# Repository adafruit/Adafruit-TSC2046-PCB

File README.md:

## Adafruit TSC2046 SPI Resistive Touch Screen Controller PCB

<a href="http://www.adafruit.com/products/5767"><br/>
Click here to purchase one from the Adafruit shop</a>

PCB files for the Adafruit TSC2046 SPI Resistive Touch Screen Controller. 

Format is EagleCAD schematic and board layout
* https://www.adafruit.com/product/5767

### Description

Getting touchy performance with your screen's touch screen? Resistive touch screens are incredibly popular as overlays to TFT and LCD displays. Only problem is they require a bunch of analog pins and you have to keep polling them since the overlays themselves are basically just big potentiometers. If your microcontroller doesn't have analog inputs, or maybe you want just a way more elegant controller, the TSC2046 is a nice way to solve that problem.

This breakout board features the TSC2046, which has an easy-to-use SPI interface available. There is also an interrupt pin that you can use to indicate when a touch has been detected to your microcontroller or microcomputer. It can be powered from 3-5V, so it's safe to use with 3V or 5V logic. It's a nicely designed chip and has very stable precise readings. We found it's also a lot faster than trying to do all the readings on an Arduino.

For the screens that have 1mm pitch FPC cables, you can plug the cable right into the connector. The majority of medium/large touchscreens have that kind of connector. If you have another kind of touch screen, the four X/Y contacts are available on 0.1" pitch breakouts so you can hand-solder or wire them.

Getting started is super easy with our simple TSC2046 Arduino library. Plug any 1mm-pitch 4-wire resistive touchscreen to the on-board FPC connector, then use the library example to read touch points with X, Y and Z (pressure) results returned instantaneously. There's an IRQ pin that will drop low when a touch is detected, you can use that to reduce the SPI polling.

We also break out the Busy pin, that lets you know when the chip is still reading, and the Vref pin if you want to read or change the default 2.5V reference voltage. There's also two extra ADC pins you can read, Aux (0V - VRef) and VBat (0V - 2*VRef).

### License

Adafruit invests time and resources providing this open source design, please support Adafruit and open-source hardware by purchasing products from [Adafruit](https://www.adafruit.com)!

Designed by Limor Fried/Ladyada for Adafruit Industries.

Creative Commons Attribution/Share-Alike, all text above must be included in any redistribution. 
See license.txt for additional details.

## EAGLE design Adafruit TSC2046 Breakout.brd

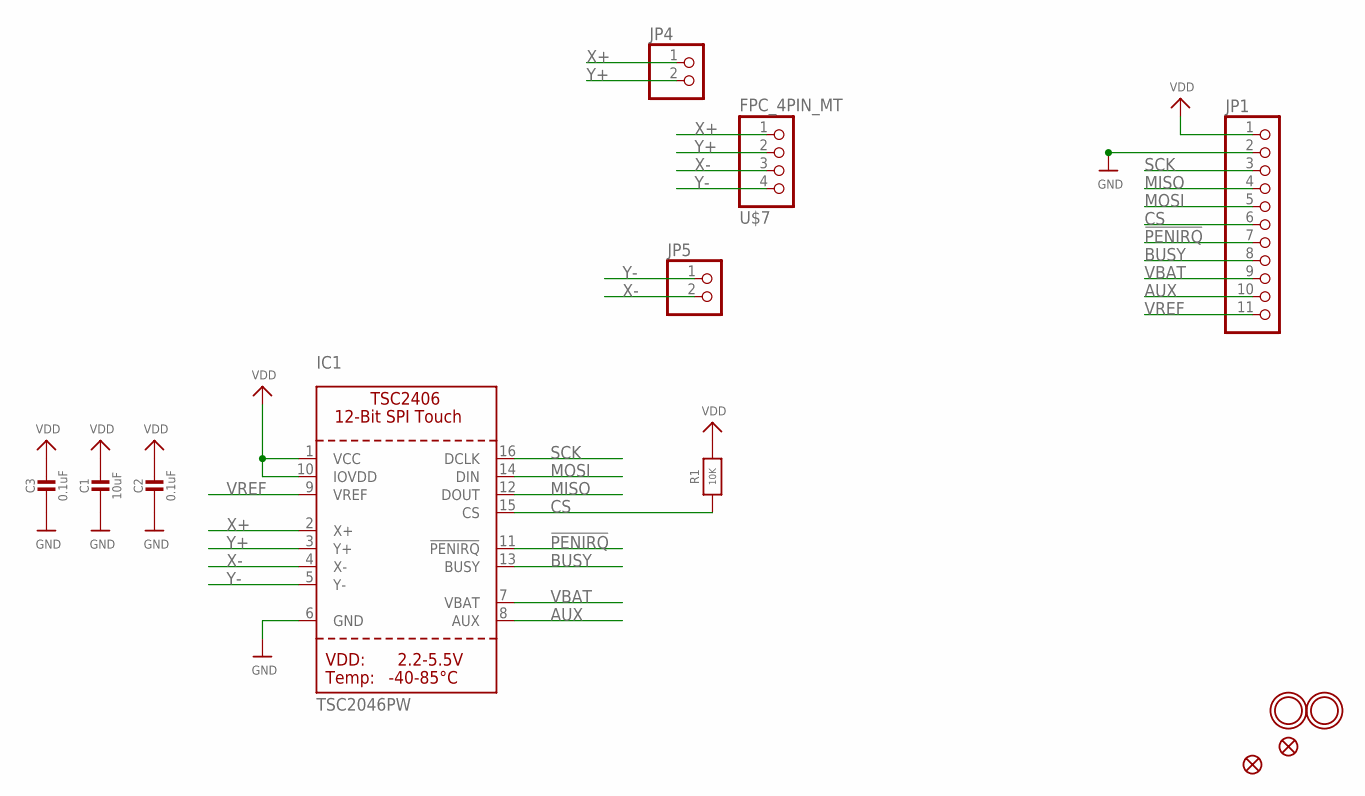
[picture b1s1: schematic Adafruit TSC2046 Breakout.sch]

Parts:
C1: 10uF; 0805-NO
C2, C3: 0.1uF; 0603-NO
FID2, FID3: FIDUCIAL_1MM
IC1: TSC2046PW; TSSOP16
JP1: HEADER-1X11; 1X11_ROUND
JP4, JP5: HEADER-1X2ROUND; 1X02_ROUND
R1: 10K; 0603-NO
U$4, U$5: MOUNTINGHOLE2.5; MOUNTINGHOLE_2.5_PLATED
U$7: FPC_4PIN_MT; FPC_CONN_1MM_DUAL_4P_MT

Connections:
!PENIRQ: IC1.11 (!PENIRQ), JP1.7
AUX: IC1.8 (AUX), JP1.10
BUSY: IC1.13 (BUSY), JP1.8
CS: IC1.15 (CS), JP1.6, R1.1
GND: C1.2, C2.2, C3.2, IC1.6 (GND), JP1.2
MISO: IC1.12 (DOUT), JP1.4
MOSI: IC1.14 (DIN), JP1.5
SCK: IC1.16 (DCLK), JP1.3
VBAT: IC1.7 (VBAT), JP1.9
VDD: C1.1, C2.1, C3.1, IC1.1 (VCC), IC1.10 (IOVDD), JP1.1, R1.2
VREF: IC1.9 (VREF), JP1.11
X+: IC1.2 (X+), JP4.1, U$7.1 (4)
X-: IC1.4 (X-), JP5.2, U$7.3 (2)
Y+: IC1.3 (Y+), JP4.2, U$7.2 (3)
Y-: IC1.5 (Y-), JP5.1, U$7.4 (1)

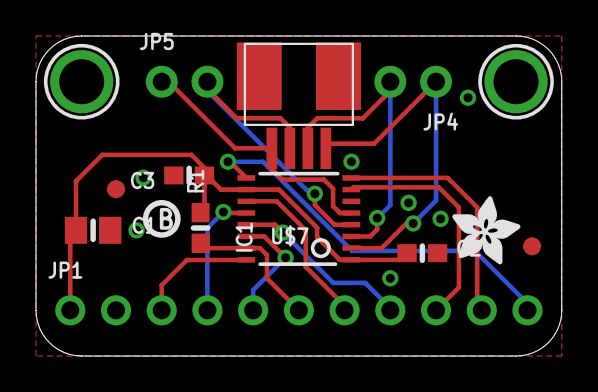
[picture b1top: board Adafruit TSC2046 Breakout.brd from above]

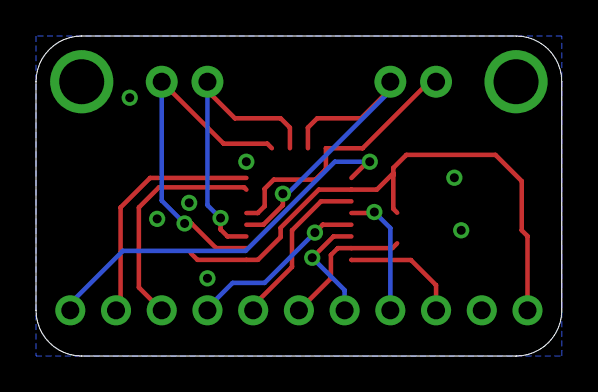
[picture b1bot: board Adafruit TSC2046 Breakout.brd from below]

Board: 2 copper layers, 29.2 x 17.8 mm, 34 parts (2 on the bottom side), 15 nets.

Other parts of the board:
PLABEL0: PLABEL0
PLABEL1: PLABEL1
PLABEL2: PLABEL2
PLABEL3: PLABEL3
PLABEL4: PLABEL4
PLABEL5: PLABEL5
PLABEL6: PLABEL6
PLABEL7: PLABEL7
PLABEL8: PLABEL8
PLABEL9: PLABEL9
PLABEL10: PLABEL10
PLABEL11: PLABEL11
PLABEL12: PLABEL12
PLABEL13: PLABEL13
PLABEL14: PLABEL14
PLABEL15: PLABEL15
PLABEL16: PLABEL16
PLABEL17: PLABEL17
PLABEL18: PLABEL18
U$6: PCBFEAT-REV-040
U$8: ADAFRUIT_3.5MM

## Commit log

2023-07-26 adding cookiecutter output

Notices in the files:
parts and their libraries:
microbuilder: This work is placed in the public domain, and may be freely used for commercial and non-commercial work with the following conditions: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
